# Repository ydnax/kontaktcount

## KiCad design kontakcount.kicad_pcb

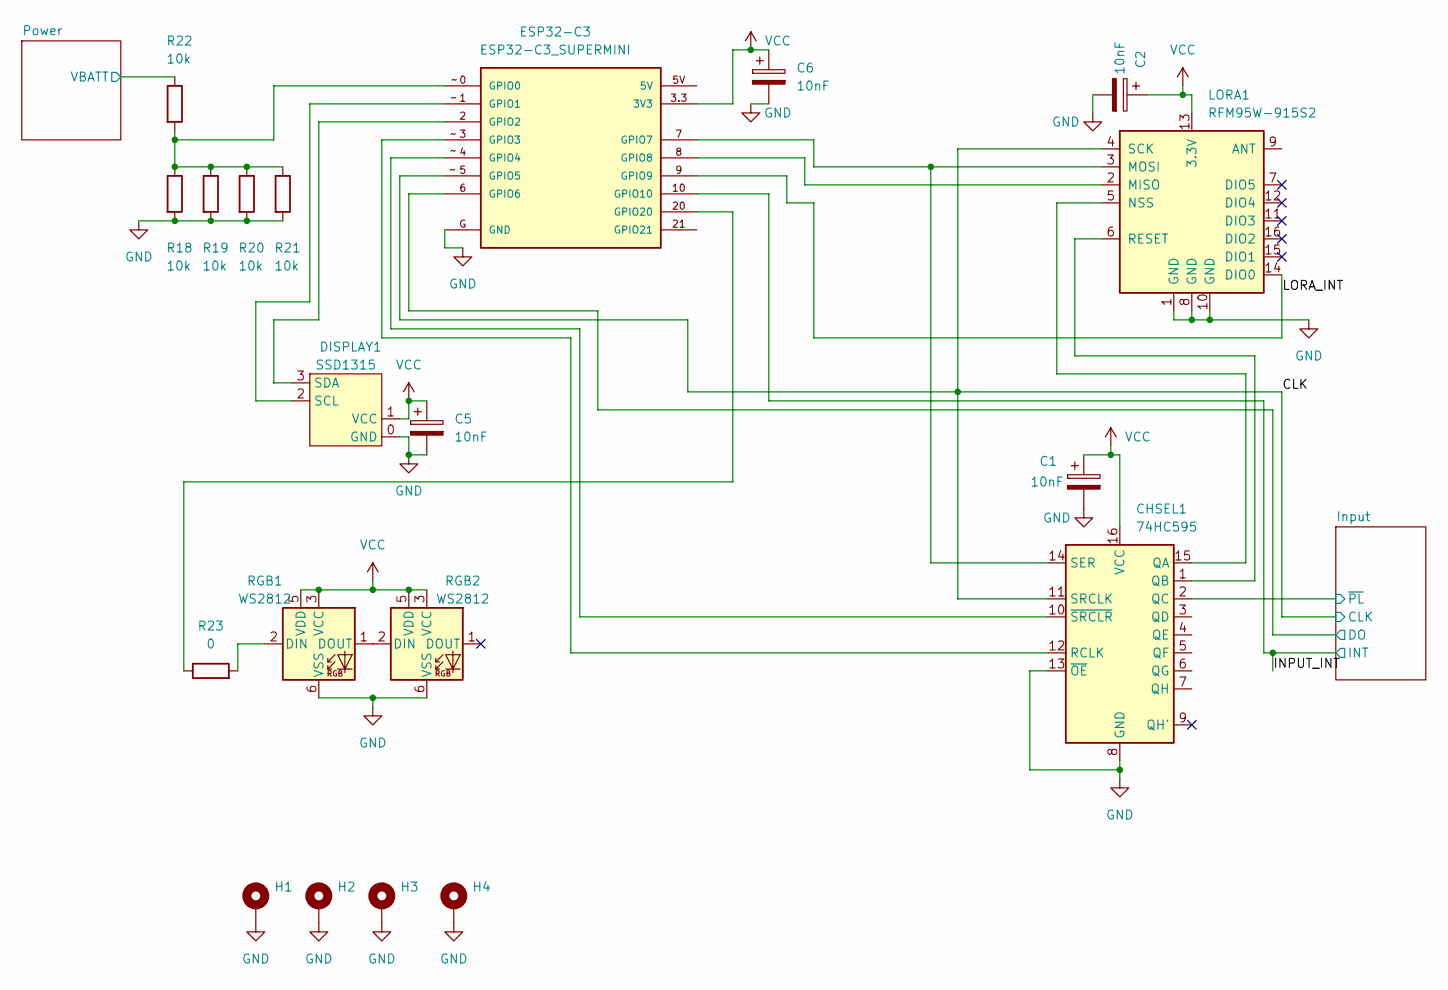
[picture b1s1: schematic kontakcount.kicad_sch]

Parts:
C1, C2, C5, C6: 10nF; C_0805_2012Metric_Pad1.18x1.45mm_HandSolder
CHSEL1: 74HC595; SOP-16_3.9x9.9mm_P1.27mm
DISPLAY1: SSD1315; SSD1315 I2C THT
ESP32-C3: ESP32-C3_SUPERMINI; MODULE_ESP32-C3_SUPERMINI SMD
H1, H2, H3, H4: MountingHole_Pad; MountingHole_3.2mm_M3_DIN965_Pad
LORA1: RFM95W-915S2; HOPERF_RFM9XW_SMD
R18, R19, R20, R21, R22: 10k; R_0805_2012Metric_Pad1.20x1.40mm_HandSolder
R23: 0; R_0805_2012Metric_Pad1.20x1.40mm_HandSolder
RGB1, RGB2: WS2812; LED_WS2812_PLCC6_5.0x5.0mm_P1.6mm

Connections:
/CLK: CHSEL1.11 (SRCLK), ESP32-C3.5 (GPIO5), LORA1.4 (SCK); also elsewhere on the board
/INPUT_INT: ESP32-C3.10 (GPIO10); also elsewhere on the board
/Input/DO: ESP32-C3.6 (GPIO6); also elsewhere on the board
/Input/~PL: CHSEL1.2 (QC); also elsewhere on the board
/LORA_INT: ESP32-C3.9 (GPIO9), LORA1.14 (DIO0)
/Power/VBATT: R22.1; also elsewhere on the board
GND: C1.2, C2.2, C5.2, C6.2, CHSEL1.8 (GND), CHSEL1.13 (~OE), DISPLAY1.0 (GND), ESP32-C3.G (GND), H1.1, H2.1, H3.1, H4.1, LORA1.1 (GND), LORA1.8 (GND), LORA1.10 (GND), R18.2, R19.2, R20.2, R21.2, RGB1.6 (VSS), RGB2.6 (VSS); also elsewhere on the board
unnamed: CHSEL1.15 (QA), LORA1.5 (NSS)
unnamed: CHSEL1.1 (QB), LORA1.6 (RESET)
unnamed: CHSEL1.12 (RCLK), ESP32-C3.3 (GPIO3)
unnamed: CHSEL1.14 (SER), ESP32-C3.7 (GPIO7), LORA1.3 (MOSI)
unnamed: CHSEL1.10 (~SRCLR), ESP32-C3.4 (GPIO4)
unnamed: DISPLAY1.2 (SCL), ESP32-C3.1 (GPIO1)
unnamed: DISPLAY1.3 (SDA), ESP32-C3.2 (GPIO2)
unnamed: ESP32-C3.0 (GPIO0), R18.1, R19.1, R20.1, R21.1, R22.2
unnamed: ESP32-C3.8 (GPIO8), LORA1.2 (MISO)
unnamed: ESP32-C3.20 (GPIO20), R23.1
unnamed: R23.2, RGB1.2 (DIN)
unnamed: RGB1.1 (DOUT), RGB2.2 (DIN)
VCC: C1.1, C2.1, C5.1, C6.1, CHSEL1.16 (VCC), DISPLAY1.1 (VCC), ESP32-C3.3.3 (3V3), LORA1.13 (3.3V), RGB1.3 (VCC), RGB1.5 (VDD), RGB2.3 (VCC), RGB2.5 (VDD); also elsewhere on the board

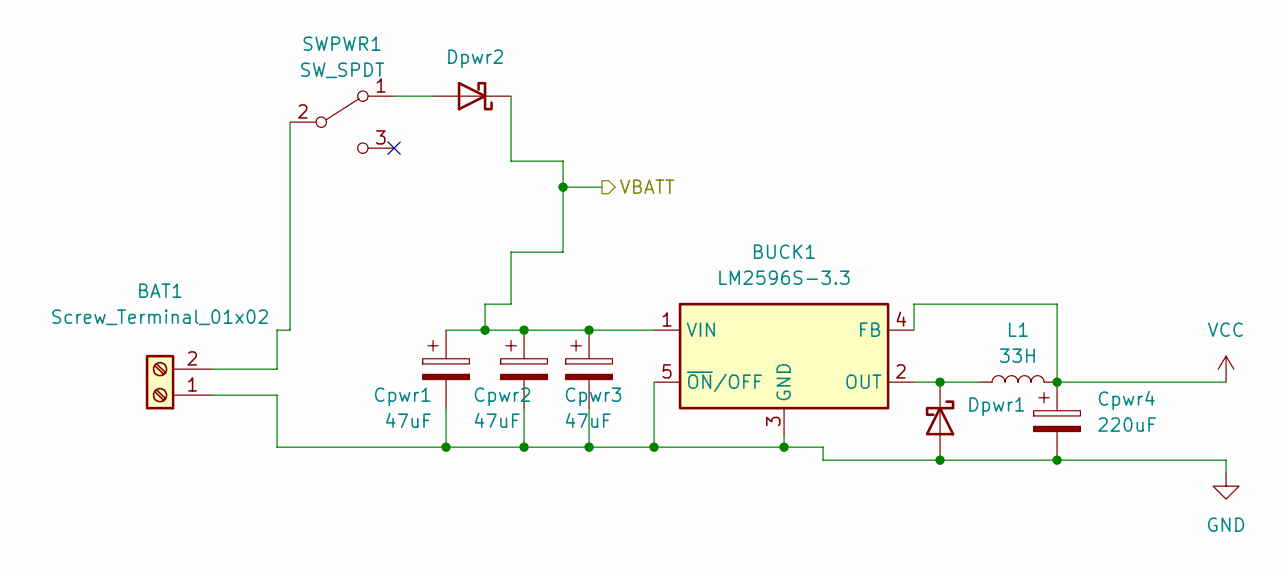
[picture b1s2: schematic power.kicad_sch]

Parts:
BAT1: Screw_Terminal_01x02; TerminalBlock_4Ucon_1x02_P3.50mm_Horizontal
BUCK1: LM2596S-3.3; TO-263-5_TabPin3
Cpwr1, Cpwr2, Cpwr3: 47uF; C_1210_3225Metric_Pad1.33x2.70mm_HandSolder
Cpwr4: 220uF; CP_EIA-3528-21_Kemet-B_Pad1.50x2.35mm_HandSolder
Dpwr1, Dpwr2: D_Schottky; D_SMA_Handsoldering
L1: 33H; L_12x12mm_H6mm
SWPWR1: SW_SPDT; POWERSWITCH SLIDE THT

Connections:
/Power/VBATT: BUCK1.1 (VIN), Cpwr1.1, Cpwr2.1, Cpwr3.1, Dpwr2.1 (K); also elsewhere on the board
GND: BAT1.1, BUCK1.3 (GND), BUCK1.5 (~ON/OFF), Cpwr1.2, Cpwr2.2, Cpwr3.2, Cpwr4.2, Dpwr1.2 (A); also elsewhere on the board
unnamed: BAT1.2, SWPWR1.2 (B)
unnamed: BUCK1.2 (OUT), Dpwr1.1 (K), L1.1
unnamed: Dpwr2.2 (A), SWPWR1.1 (A)
VCC: BUCK1.4 (FB), Cpwr4.1, L1.2; also elsewhere on the board

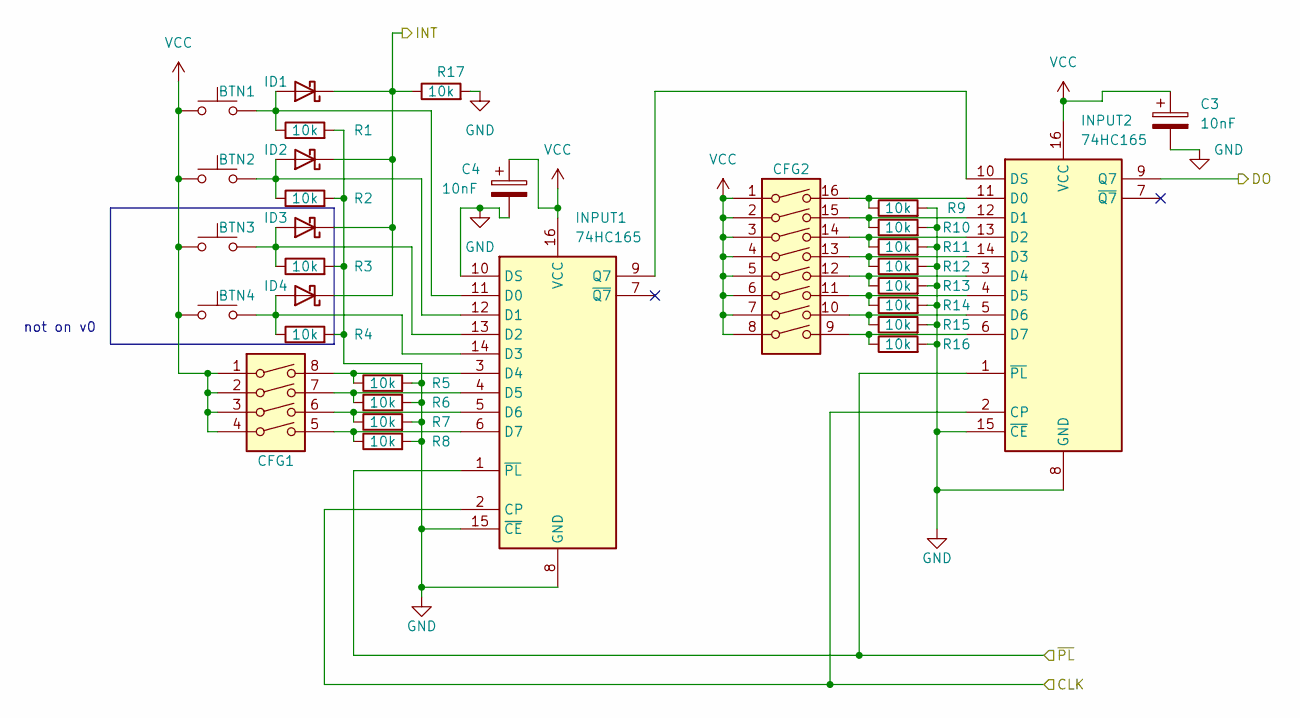
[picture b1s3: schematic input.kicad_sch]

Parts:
BTN1, BTN2, BTN3, BTN4: SW_Push; SW_Cherry_MX_1.00u_PCB
C3, C4: 10nF; C_0805_2012Metric_Pad1.18x1.45mm_HandSolder
CFG1: SW_DIP_x04; SW_DIP_SPSTx04_Slide_9.78x12.34mm_W7.62mm_P2.54mm
CFG2: SW_DIP_x08; SW_DIP_SPSTx08_Slide_9.78x22.5mm_W7.62mm_P2.54mm
ID1, ID2, ID3, ID4: D_Schottky; D_SMA_Handsoldering
INPUT1, INPUT2: 74HC165; SOP-16_3.9x9.9mm_P1.27mm
R1, R2, R3, R4, R5, R6, R7, R8, R9, R10, R11, R12, R13, R14, R15, R16, R17: 10k; R_0805_2012Metric_Pad1.20x1.40mm_HandSolder

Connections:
/CLK: INPUT1.2 (CP), INPUT2.2 (CP); also elsewhere on the board
/INPUT_INT: ID1.1 (K), ID2.1 (K), ID3.1 (K), ID4.1 (K), R17.1; also elsewhere on the board
/Input/DO: INPUT2.9 (Q7); also elsewhere on the board
/Input/~PL: INPUT1.1 (~PL), INPUT2.1 (~PL); also elsewhere on the board
GND: C3.2, C4.2, INPUT1.8 (GND), INPUT1.10 (DS), INPUT1.15 (~CE), INPUT2.8 (GND), INPUT2.15 (~CE), R1.2, R2.2, R3.2, R4.2, R5.2, R6.2, R7.2, R8.2, R9.2, R10.2, R11.2, R12.2, R13.2, R14.2, R15.2, R16.2, R17.2; also elsewhere on the board
unnamed: BTN1.2, ID1.2 (A), INPUT1.11 (D0), R1.1
unnamed: BTN2.2, ID2.2 (A), INPUT1.12 (D1), R2.1
unnamed: BTN3.2, ID3.2 (A), INPUT1.13 (D2), R3.1
unnamed: BTN4.2, ID4.2 (A), INPUT1.14 (D3), R4.1
unnamed: CFG1.8, INPUT1.3 (D4), R5.1
unnamed: CFG1.7, INPUT1.4 (D5), R6.1
unnamed: CFG1.6, INPUT1.5 (D6), R7.1
unnamed: CFG1.5, INPUT1.6 (D7), R8.1
unnamed: INPUT1.9 (Q7), INPUT2.10 (DS)
unnamed: CFG2.16, INPUT2.11 (D0), R9.1
unnamed: CFG2.15, INPUT2.12 (D1), R10.1
unnamed: CFG2.14, INPUT2.13 (D2), R11.1
unnamed: CFG2.13, INPUT2.14 (D3), R12.1
unnamed: CFG2.12, INPUT2.3 (D4), R13.1
unnamed: CFG2.11, INPUT2.4 (D5), R14.1
unnamed: CFG2.10, INPUT2.5 (D6), R15.1
unnamed: CFG2.9, INPUT2.6 (D7), R16.1
VCC: BTN1.1, BTN2.1, BTN3.1, BTN4.1, C3.1, C4.1, CFG1.1, CFG1.2, CFG1.3, CFG1.4, CFG2.1, CFG2.2, CFG2.3, CFG2.4, CFG2.5, CFG2.6, CFG2.7, CFG2.8, INPUT1.16 (VCC), INPUT2.16 (VCC); also elsewhere on the board

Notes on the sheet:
not on v0

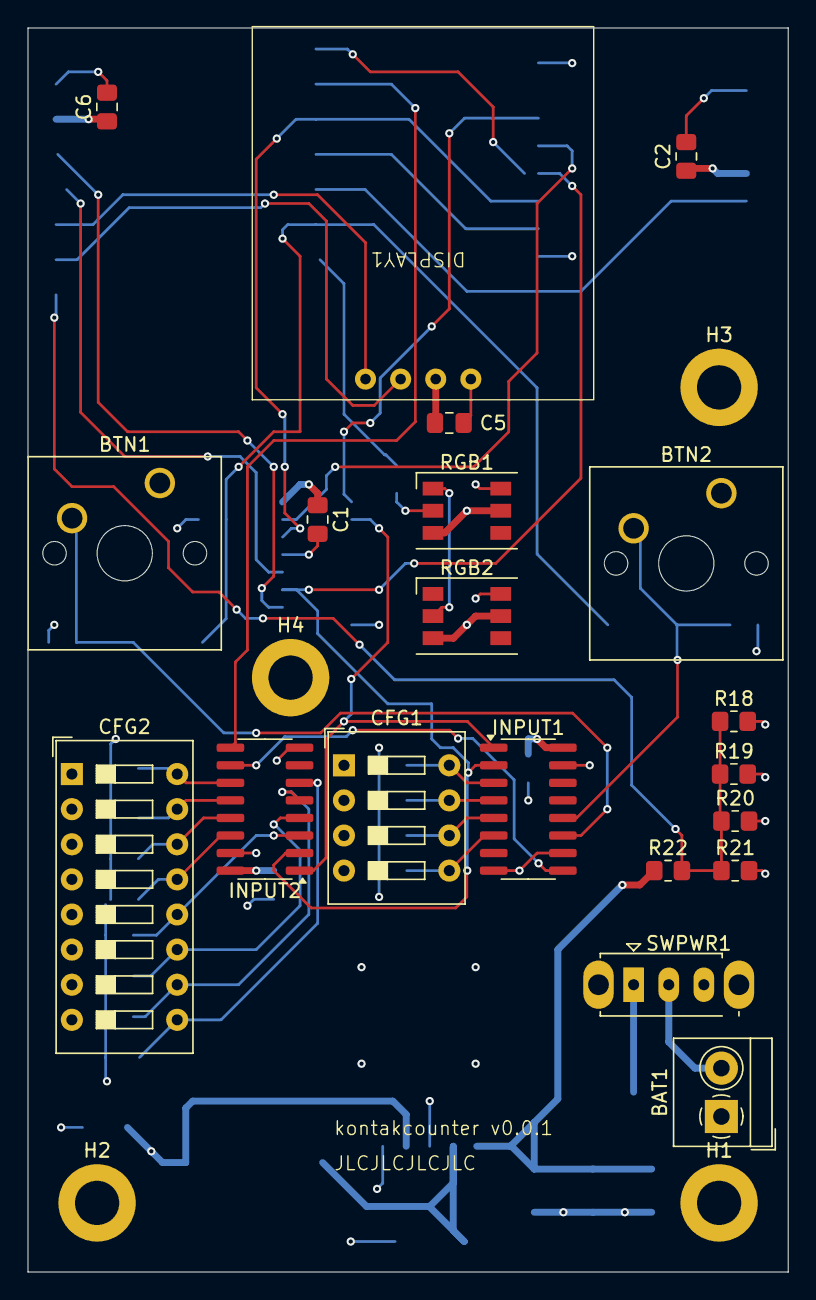
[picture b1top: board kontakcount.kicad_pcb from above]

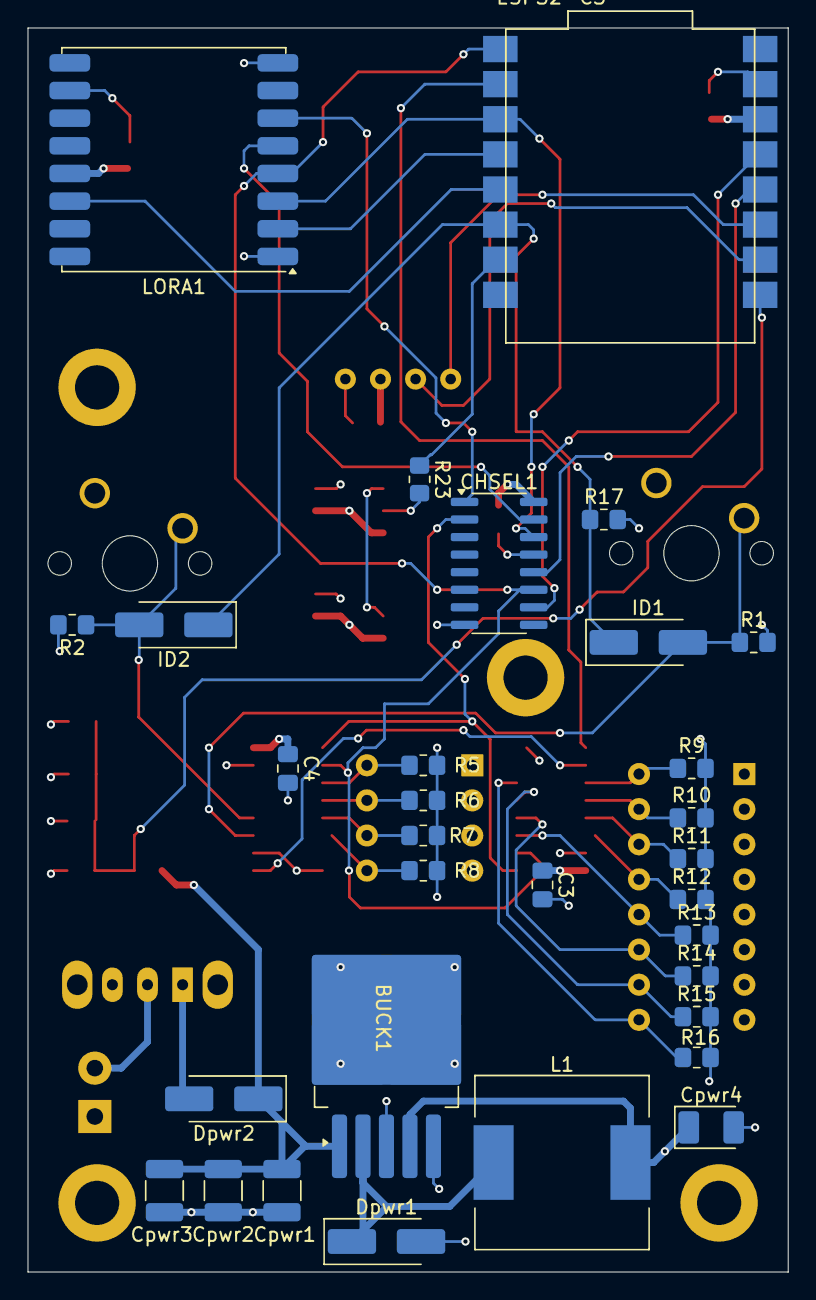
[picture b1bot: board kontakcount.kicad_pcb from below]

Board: 4 copper layers, 55.0 x 90.0 mm, 55 parts (31 on the bottom side), 38 nets.

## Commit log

2024-04-24 initial draft, autorouted
2024-04-24 add README
2024-04-25 routing progress towards v001
2024-04-25 v0.0.1
